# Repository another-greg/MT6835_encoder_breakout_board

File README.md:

# MT6835_encoder_breakout_board
A simple breakout board for using the MT6835 magnetic encoder. 

## How to use the board
See [schematic](./magnetic_encoder_schematic.pdf) for more details
### Inputs/Outputs
The connections are broken out into 3 JST-PH connectors
  - 6 pin: SPI and power input (mandatory- need 3.3 or 5V to power board)
  - 4 pin: ABZ/PWM output
  - 3 pin: UVW output

The thinking being you will need to connect via SPI to configure the encoder no matter what, but likely you'll use either ABZ or UVW for monitoring position.

## How to order 
The BOM for this design was optimized around in-stock JLCPCB parts. To order this board, simply make a zip of the "JLCPCB" folder and upload to the JLCPCB order page.

## Schematic

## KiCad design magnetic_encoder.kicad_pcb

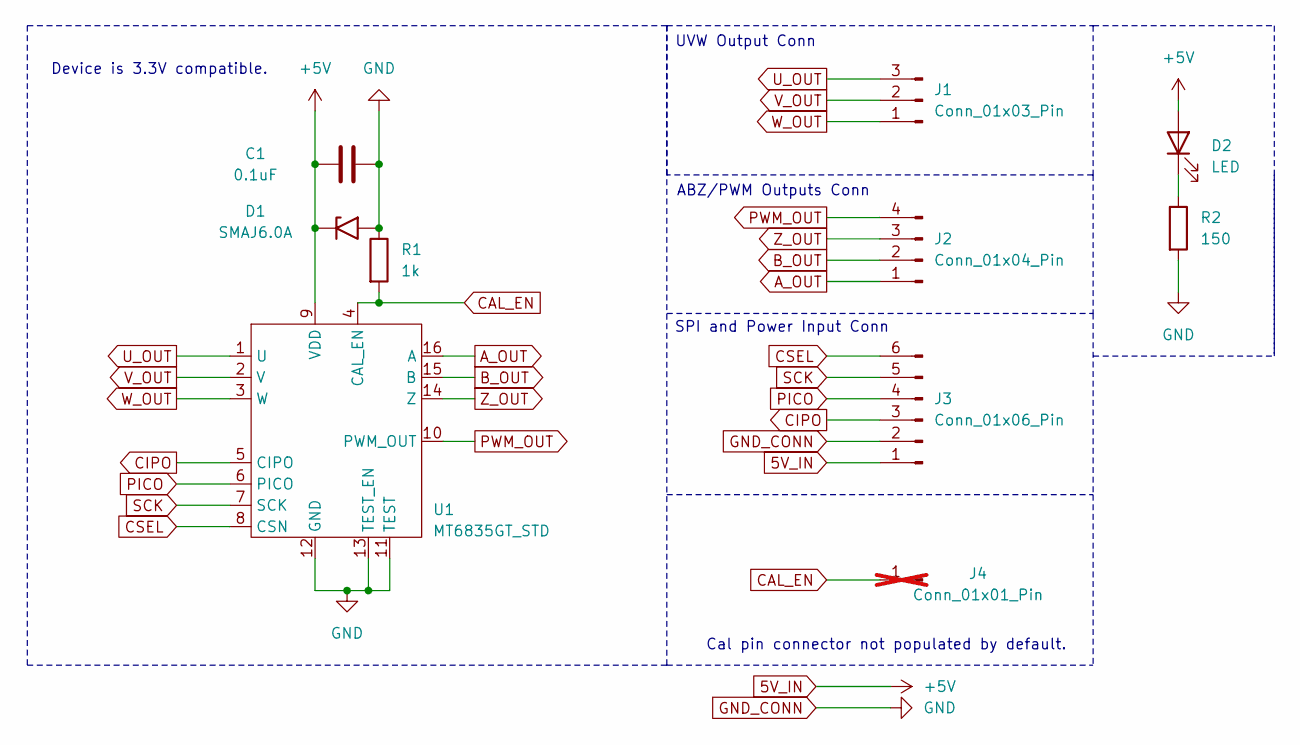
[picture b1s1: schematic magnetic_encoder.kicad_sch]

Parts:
C1: 0.1uF; C_0603_1608Metric
D1: SMAJ6.0A; D_SMA
D2: LED; LED_0603_1608Metric
J1: Conn_01x03_Pin; JST_PH_S3B-PH-SM4-TB_1x03-1MP_P2.00mm_Horizontal
J2: Conn_01x04_Pin; JST_PH_S4B-PH-SM4-TB_1x04-1MP_P2.00mm_Horizontal
J3: Conn_01x06_Pin; JST_PH_S6B-PH-SM4-TB_1x06-1MP_P2.00mm_Horizontal
J4: Conn_01x01_Pin; PinHeader_1x01_P2.54mm_Vertical; not fitted
R1: 1k; R_0402_1005Metric
R2: 150; R_0402_1005Metric
U1: MT6835GT_STD; TSSOP-16_4.4x5mm_P0.65mm

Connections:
5V_IN: C1.1, D1.1 (A1), D2.2 (A), J3.1, U1.9 (VDD)
A_OUT: J2.1, U1.16 (A)
B_OUT: J2.2, U1.15 (B)
CAL_EN: J4.1, R1.2, U1.4 (CAL_EN)
CIPO: J3.3, U1.5 (CIPO)
CSEL: J3.6, U1.8 (CSN)
GND_CONN: C1.2, D1.2 (A2), J3.2, R1.1, R2.2, U1.11 (TEST), U1.12 (GND), U1.13 (TEST_EN)
unnamed: D2.1 (K), R2.1
PICO: J3.4, U1.6 (PICO)
PWM_OUT: J2.4, U1.10 (PWM_OUT)
SCK: J3.5, U1.7 (SCK)
U_OUT: J1.3, U1.1 (U)
V_OUT: J1.2, U1.2 (V)
W_OUT: J1.1, U1.3 (W)
Z_OUT: J2.3, U1.14 (Z)

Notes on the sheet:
Cal pin connector not populated by default.
ABZ/PWM Outputs Conn
SPI and Power Input Conn
Device is 3.3V compatible.
UVW Output Conn

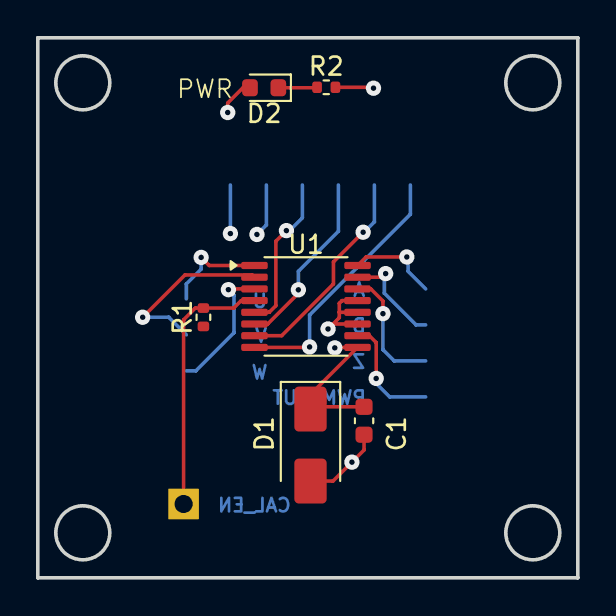
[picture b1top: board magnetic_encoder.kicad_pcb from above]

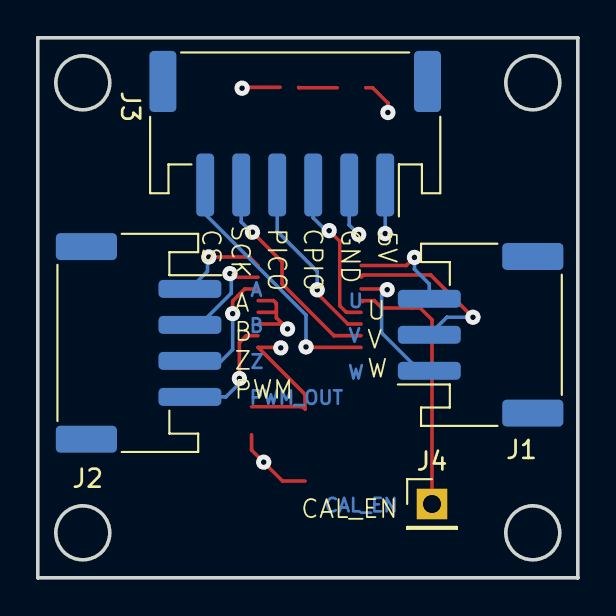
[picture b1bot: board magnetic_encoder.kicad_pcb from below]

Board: 4 copper layers, 30.0 x 30.0 mm, 10 parts (4 on the bottom side), 15 nets.

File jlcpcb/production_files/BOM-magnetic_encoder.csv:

Comment,Designator,Footprint,LCSC,Quantity
0.1uF,C1,C_0603_1608Metric,C125205,1
150,R2,R_0402_1005Metric,C25082,1
1k,R1,R_0402_1005Metric,C25543,1
Conn_01x03_Pin,J1,JST_PH_S3B-PH-SM4-TB_1x03-1MP_P2.00mm_Horizontal,C265101,1
Conn_01x04_Pin,J2,JST_PH_S4B-PH-SM4-TB_1x04-1MP_P2.00mm_Horizontal,C265102,1
Conn_01x06_Pin,J3,JST_PH_S6B-PH-SM4-TB_1x06-1MP_P2.00mm_Horizontal,C265405,1
LED,D2,LED_0603_1608Metric,C2290,1
MT6835GT_STD,U1,TSSOP-16_4.4x5mm_P0.65mm,C2932578,1
SMAJ6.0A,D1,D_SMA,C110522,1
Conn_01x01_Pin,,PinHeader_1x01_P2.54mm_Vertical,,0

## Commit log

2026-04-14 add image of schematic
2026-04-14 uploaded images
2026-04-14 added labels to pins
